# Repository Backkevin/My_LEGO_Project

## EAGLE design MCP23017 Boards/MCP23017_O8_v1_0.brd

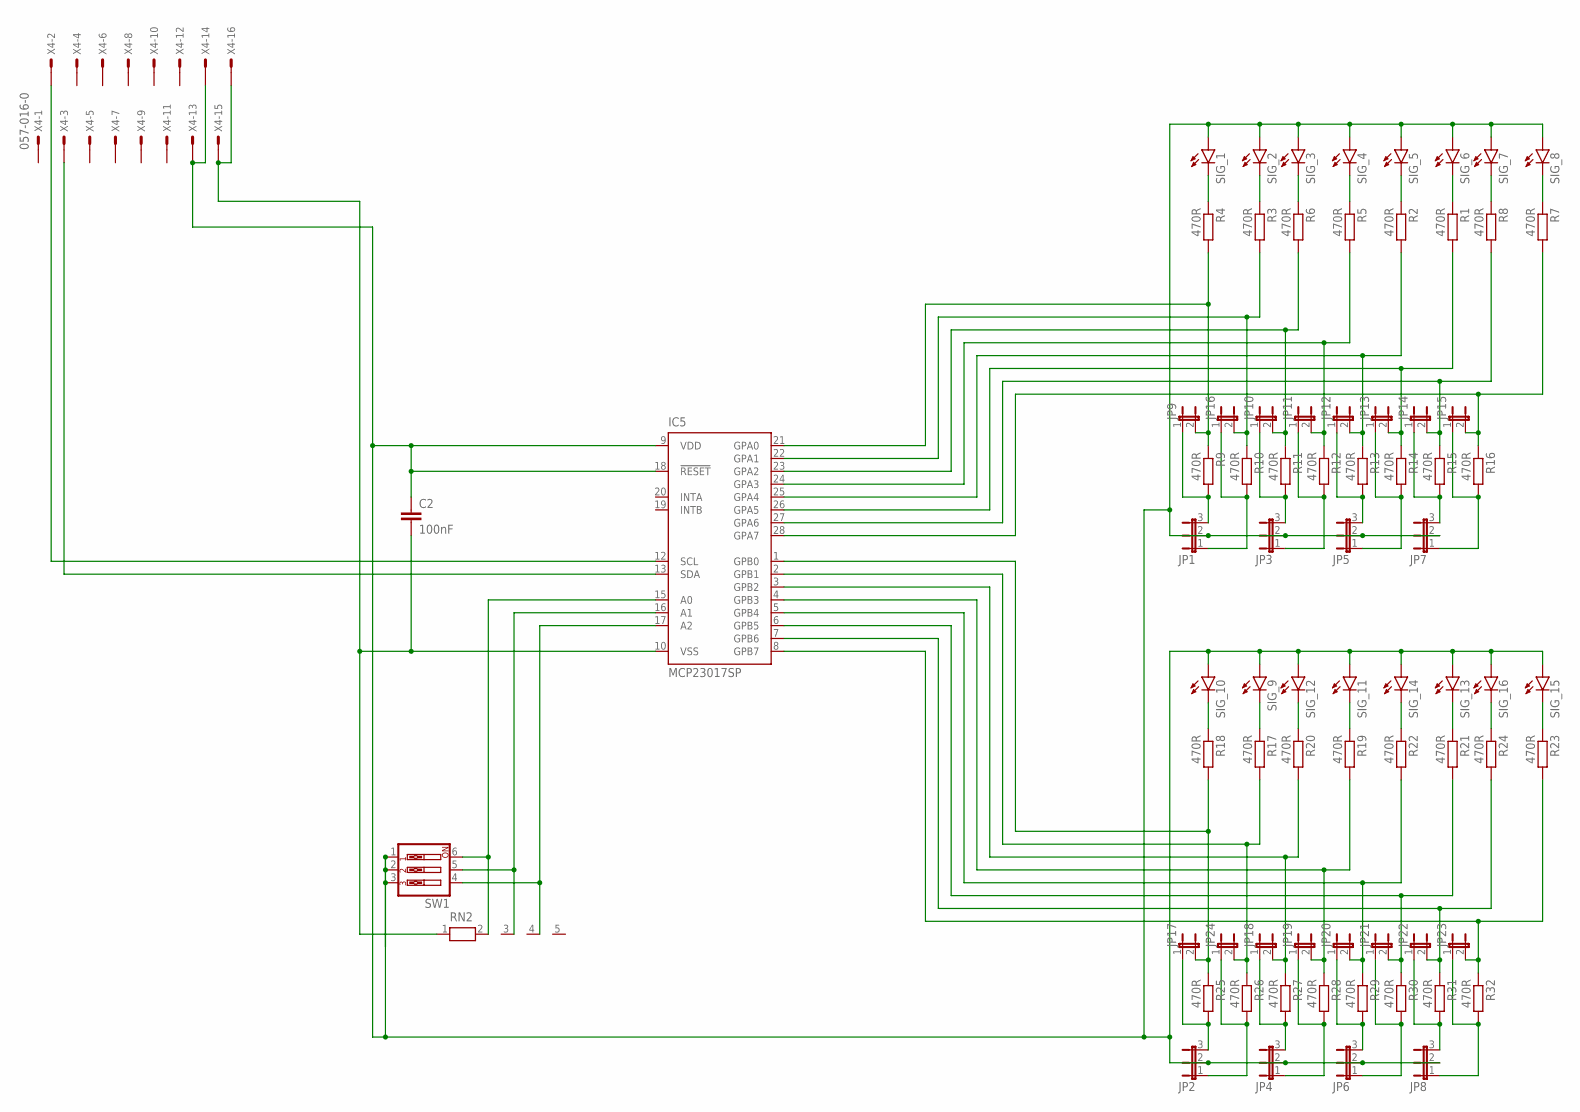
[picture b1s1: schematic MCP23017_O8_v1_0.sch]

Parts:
C2: 100nF; C025-024X044
IC5: MCP23017SP; DIL28-3
JP1, JP2, JP3, JP4, JP5, JP6, JP7, JP8: JP2E; JP2
JP9, JP10, JP11, JP12, JP13, JP14, JP15, JP16, JP17, JP18, JP19, JP20, JP21, JP22, JP23, JP24: JP1E; JP1
R1, R2, R3, R4, R5, R6, R7, R8, R9, R10, R11, R12, R13, R14, R15, R16, R17, R18, R19, R20, R21, R22, R23, R24, R25, R26, R27, R28, R29, R30, R31, R32: 470R; 0309/10
RN2: RN04; RN-5
SIG_1, SIG_2, SIG_3, SIG_4, SIG_5, SIG_6, SIG_7, SIG_8, SIG_9, SIG_10, SIG_11, SIG_12, SIG_13, SIG_14, SIG_15, SIG_16: LED3MM
SW1: SW_DIP-3; EDG-03
X4: 057-016-0

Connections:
GND2: C2.2, IC5.10 (VSS), RN2.1, X4.15, X4.16
unnamed: JP1.3, JP9.1, R9.2
unnamed: R2.1, SIG_5.K (C)
unnamed: R1.1, SIG_6.K (C)
unnamed: IC5.27 (GPA6), JP14.2, R8.2, R15.1
unnamed: IC5.17 (A2), RN2.4, SW1.4
unnamed: R8.1, SIG_7.K (C)
unnamed: R7.1, SIG_8.K (C)
unnamed: JP1.1, JP16.1, R10.2
unnamed: JP3.3, JP10.1, R11.2
unnamed: JP3.1, JP11.1, R12.2
unnamed: JP5.3, JP12.1, R13.2
unnamed: IC5.22 (GPA1), JP16.2, R3.2, R10.1
unnamed: IC5.24 (GPA3), JP11.2, R5.2, R12.1
unnamed: IC5.26 (GPA5), JP13.2, R1.2, R14.1
unnamed: IC5.28 (GPA7), JP15.2, R7.2, R16.1
unnamed: IC5.21 (GPA0), JP9.2, R4.2, R9.1
unnamed: JP5.1, JP13.1, R14.2
unnamed: JP7.3, JP14.1, R15.2
unnamed: JP7.1, JP15.1, R16.2
unnamed: IC5.16 (A1), RN2.3, SW1.5
unnamed: R4.1, SIG_1.K (C)
unnamed: R3.1, SIG_2.K (C)
unnamed: IC5.23 (GPA2), JP10.2, R6.2, R11.1
unnamed: IC5.25 (GPA4), JP12.2, R2.2, R13.1
unnamed: IC5.1 (GPB0), JP17.2, R18.2, R25.1
unnamed: IC5.3 (GPB2), JP18.2, R20.2, R27.1
unnamed: R6.1, SIG_3.K (C)
unnamed: R5.1, SIG_4.K (C)
unnamed: IC5.6 (GPB5), JP21.2, R21.2, R30.1
unnamed: IC5.8 (GPB7), JP23.2, R23.2, R32.1
unnamed: IC5.2 (GPB1), JP24.2, R17.2, R26.1
unnamed: R18.1, SIG_10.K (C)
unnamed: R17.1, SIG_9.K (C)
unnamed: IC5.4 (GPB3), JP19.2, R19.2, R28.1
unnamed: IC5.5 (GPB4), JP20.2, R22.2, R29.1
unnamed: R20.1, SIG_12.K (C)
unnamed: R19.1, SIG_11.K (C)
unnamed: R22.1, SIG_14.K (C)
unnamed: R21.1, SIG_13.K (C)
unnamed: IC5.7 (GPB6), JP22.2, R24.2, R31.1
unnamed: R24.1, SIG_16.K (C)
unnamed: R23.1, SIG_15.K (C)
unnamed: JP2.3, JP17.1, R25.2
unnamed: JP2.1, JP24.1, R26.2
unnamed: JP4.3, JP18.1, R27.2
unnamed: JP4.1, JP19.1, R28.2
unnamed: JP6.3, JP20.1, R29.2
unnamed: JP6.1, JP21.1, R30.2
unnamed: JP8.3, JP22.1, R31.2
unnamed: JP8.1, JP23.1, R32.2
unnamed: IC5.12 (SCL), X4.2
unnamed: IC5.13 (SDA), X4.3
unnamed: IC5.15 (A0), RN2.2, SW1.6
VCC5.1: C2.1, IC5.9 (VDD), IC5.18 (!RESET), JP1.2, JP2.2, JP3.2, JP4.2, JP5.2, JP6.2, JP7.2, JP8.2, SIG_1.A, SIG_2.A, SIG_3.A, SIG_4.A, SIG_5.A, SIG_6.A, SIG_7.A, SIG_8.A, SIG_9.A, SIG_10.A, SIG_11.A, SIG_12.A, SIG_13.A, SIG_14.A, SIG_15.A, SIG_16.A, SW1.1, SW1.2, SW1.3, X4.13, X4.14

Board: 2 copper layers, 77 parts (0 on the bottom side), 55 nets, no tracks yet.

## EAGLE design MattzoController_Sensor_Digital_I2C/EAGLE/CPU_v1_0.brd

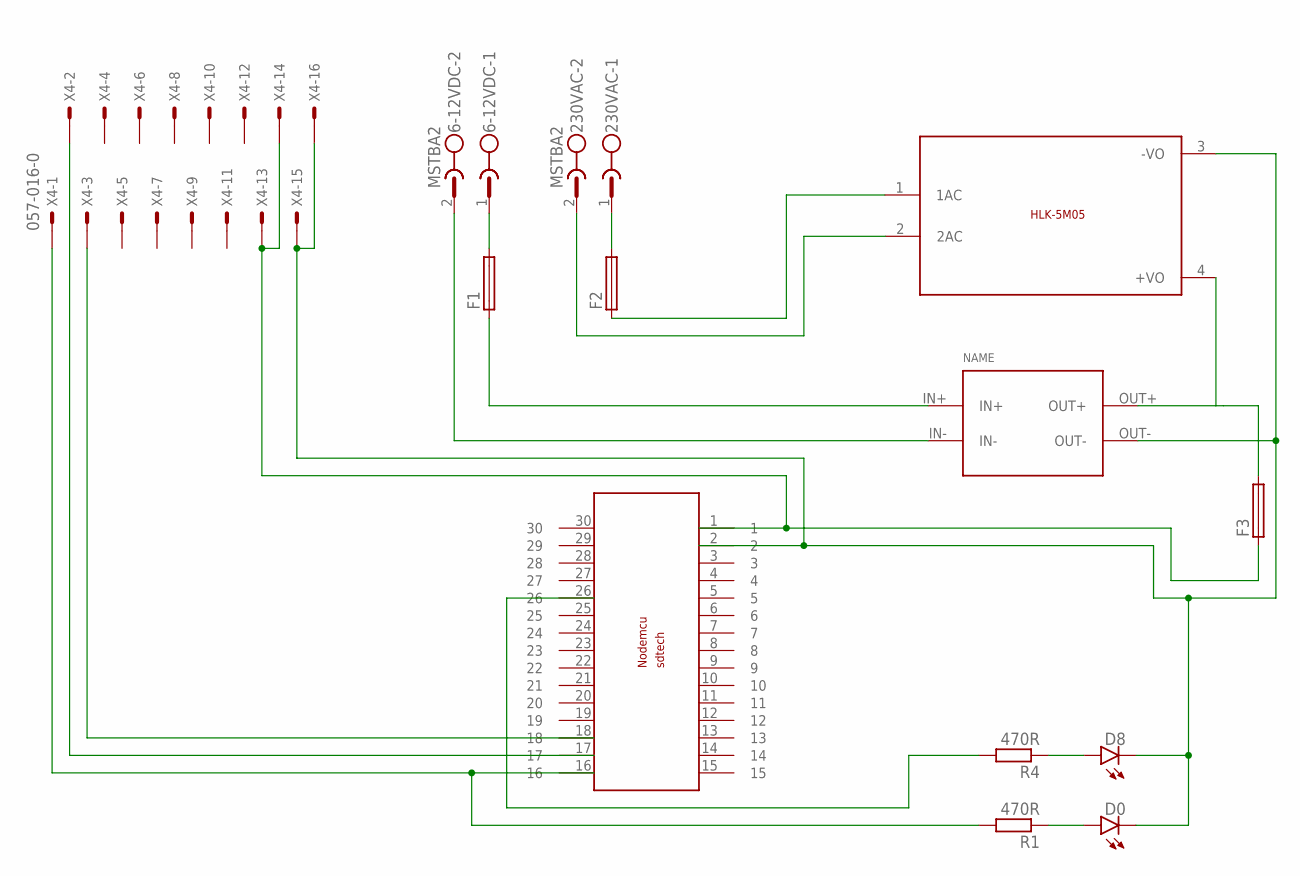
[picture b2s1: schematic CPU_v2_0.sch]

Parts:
6-12VDC, 230VAC: MSTBA2
D0, D8: LED3MM
F1, F2, F3: SH22,5A
R1, R4: 470R; 0309/10
U$1: NODEMCUESP8266
U$2: CP8-ADJ
U$3: 5VDC/5W; HLK-5M05
X4: 057-016-0

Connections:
+5VDC: F3.1, U$1.1, X4.13, X4.14
D0: R1.2, U$1.16, X4.1
D8: R4.2, U$1.26
GND: D0.K (C), D8.K (C), U$1.2, U$2.OUT-, U$3.3 (-VO), X4.15, X4.16
unnamed: D8.A, R4.1
unnamed: F3.2, U$2.OUT+, U$3.4 (+VO)
unnamed: D0.A, R1.1
unnamed: 230VAC.1, F2.2
unnamed: F2.1, U$3.1 (1AC)
unnamed: 230VAC.2, U$3.2 (2AC)
unnamed: 6-12VDC.1, F1.2
unnamed: F1.1, U$2.IN+
unnamed: 6-12VDC.2, U$2.IN-
SCL: U$1.17, X4.2
SDA: U$1.18, X4.3

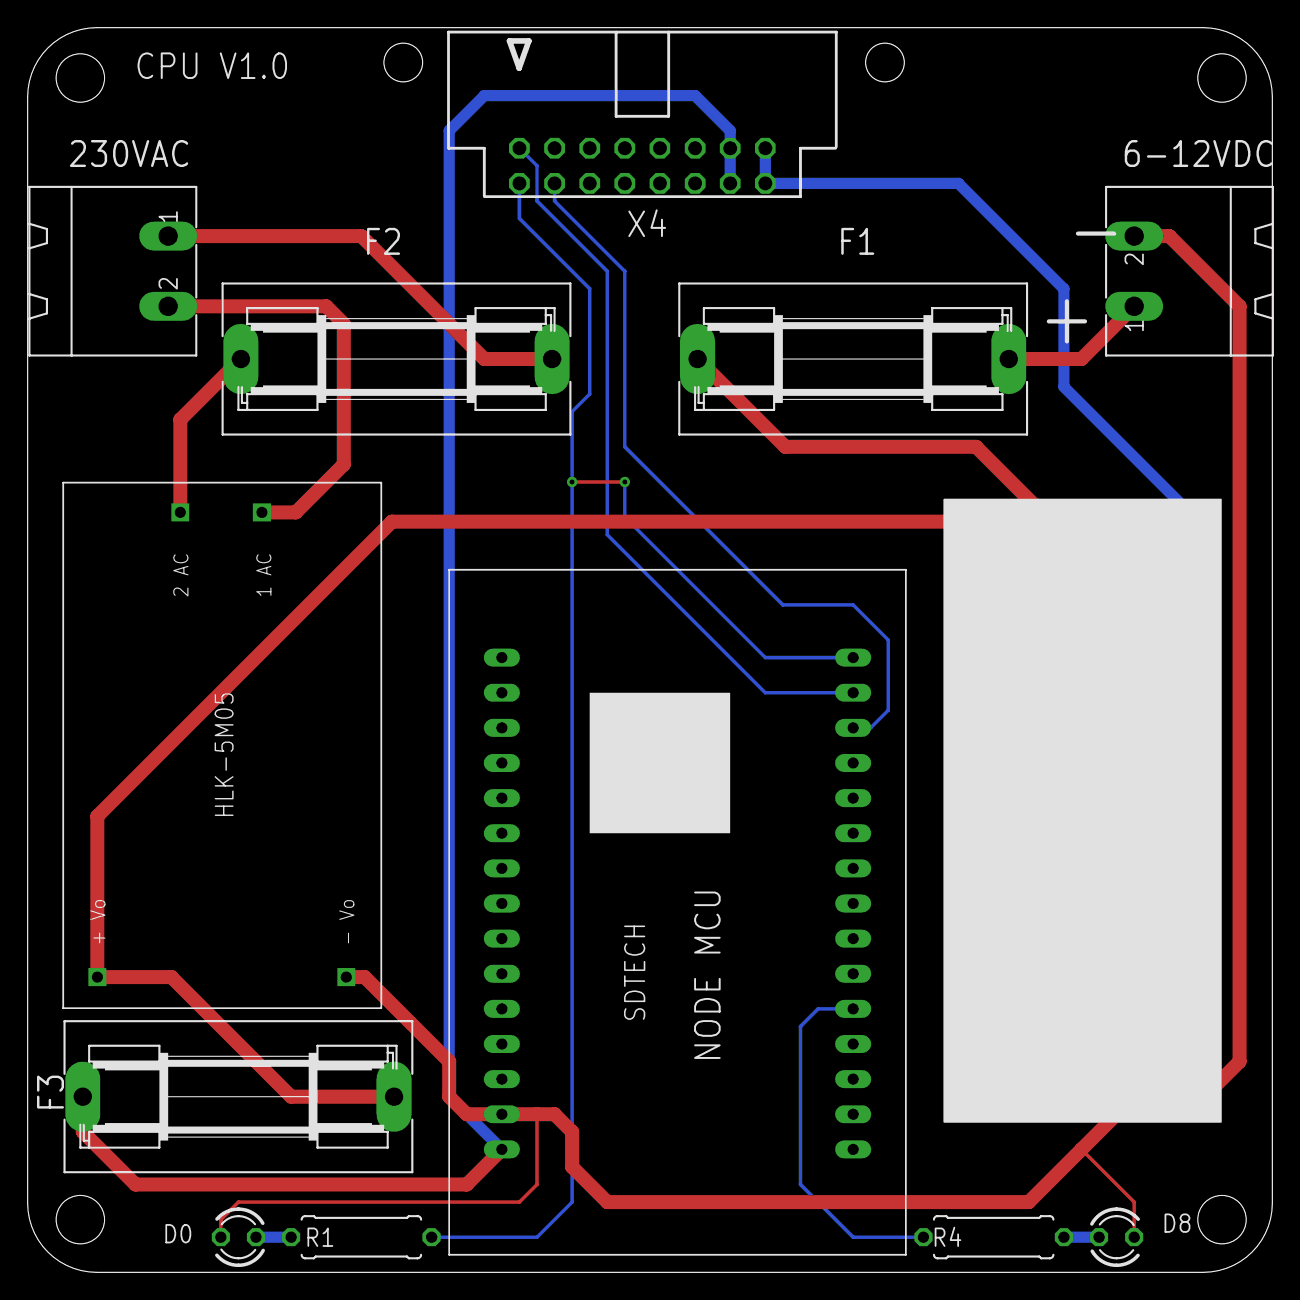
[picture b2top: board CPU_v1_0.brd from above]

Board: 2 copper layers, 90.0 x 90.0 mm, 13 parts (0 on the bottom side), 15 nets.

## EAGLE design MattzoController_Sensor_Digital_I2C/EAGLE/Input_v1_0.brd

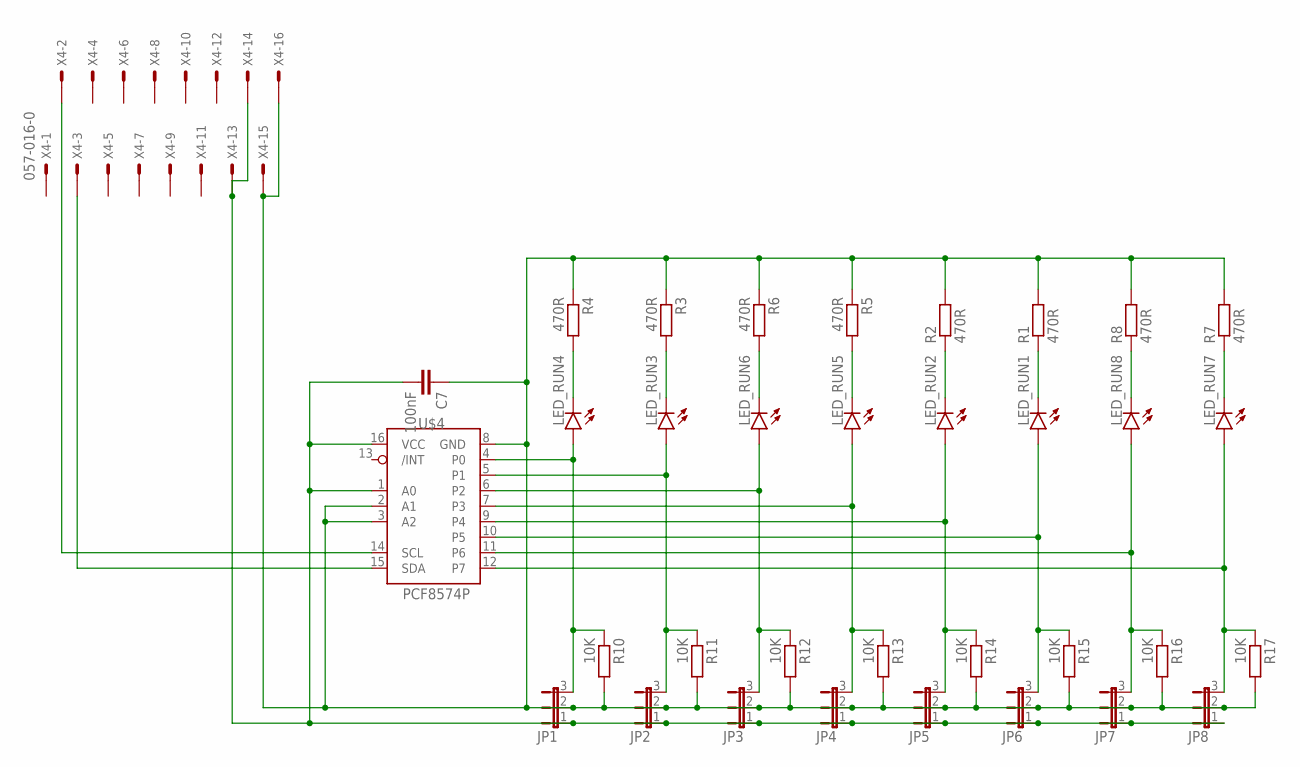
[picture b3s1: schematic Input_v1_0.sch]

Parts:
C7: 100nF; C025-024X044
JP1, JP2, JP3, JP4, JP5, JP6, JP7, JP8: JP2E; JP2
LED_RUN1, LED_RUN2, LED_RUN3, LED_RUN4, LED_RUN5, LED_RUN6, LED_RUN7, LED_RUN8: LED3MM
R1, R2, R3, R4, R5, R6, R7, R8: 470R; 0309/10
R10, R11, R12, R13, R14, R15, R16, R17: 10K; 0309/10
U$4: PCF8574P; DIL16
X4: 057-016-0

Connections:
GND1: C7.1, JP1.2, JP2.2, JP3.2, JP4.2, JP5.2, JP6.2, JP7.2, JP8.2, R1.2, R2.2, R3.1, R4.1, R5.1, R6.1, R7.2, R8.2, R10.2, R11.2, R12.2, R13.2, R14.2, R15.2, R16.2, R17.2, U$4.2 (A1), U$4.3 (A2), U$4.8 (GND), X4.15, X4.16
unnamed: LED_RUN7.K (C), R7.1
unnamed: LED_RUN8.K (C), R8.1
unnamed: LED_RUN1.K (C), R1.1
unnamed: LED_RUN2.K (C), R2.1
unnamed: LED_RUN5.K (C), R5.2
unnamed: LED_RUN6.K (C), R6.2
unnamed: LED_RUN3.K (C), R3.2
unnamed: LED_RUN4.K (C), R4.2
unnamed: U$4.15 (SDA), X4.3
unnamed: JP1.3, LED_RUN4.A, R10.1, U$4.4 (P0)
unnamed: JP2.3, LED_RUN3.A, R11.1, U$4.5 (P1)
unnamed: JP3.3, LED_RUN6.A, R12.1, U$4.6 (P2)
unnamed: JP4.3, LED_RUN5.A, R13.1, U$4.7 (P3)
unnamed: JP5.3, LED_RUN2.A, R14.1, U$4.9 (P4)
unnamed: JP6.3, LED_RUN1.A, R15.1, U$4.10 (P5)
unnamed: JP7.3, LED_RUN8.A, R16.1, U$4.11 (P6)
unnamed: JP8.3, LED_RUN7.A, R17.1, U$4.12 (P7)
SCL: U$4.14 (SCL), X4.2
VCC5.0: C7.2, JP1.1, JP2.1, JP3.1, JP4.1, JP5.1, JP6.1, JP7.1, JP8.1, U$4.1 (A0), U$4.16 (VCC), X4.13, X4.14

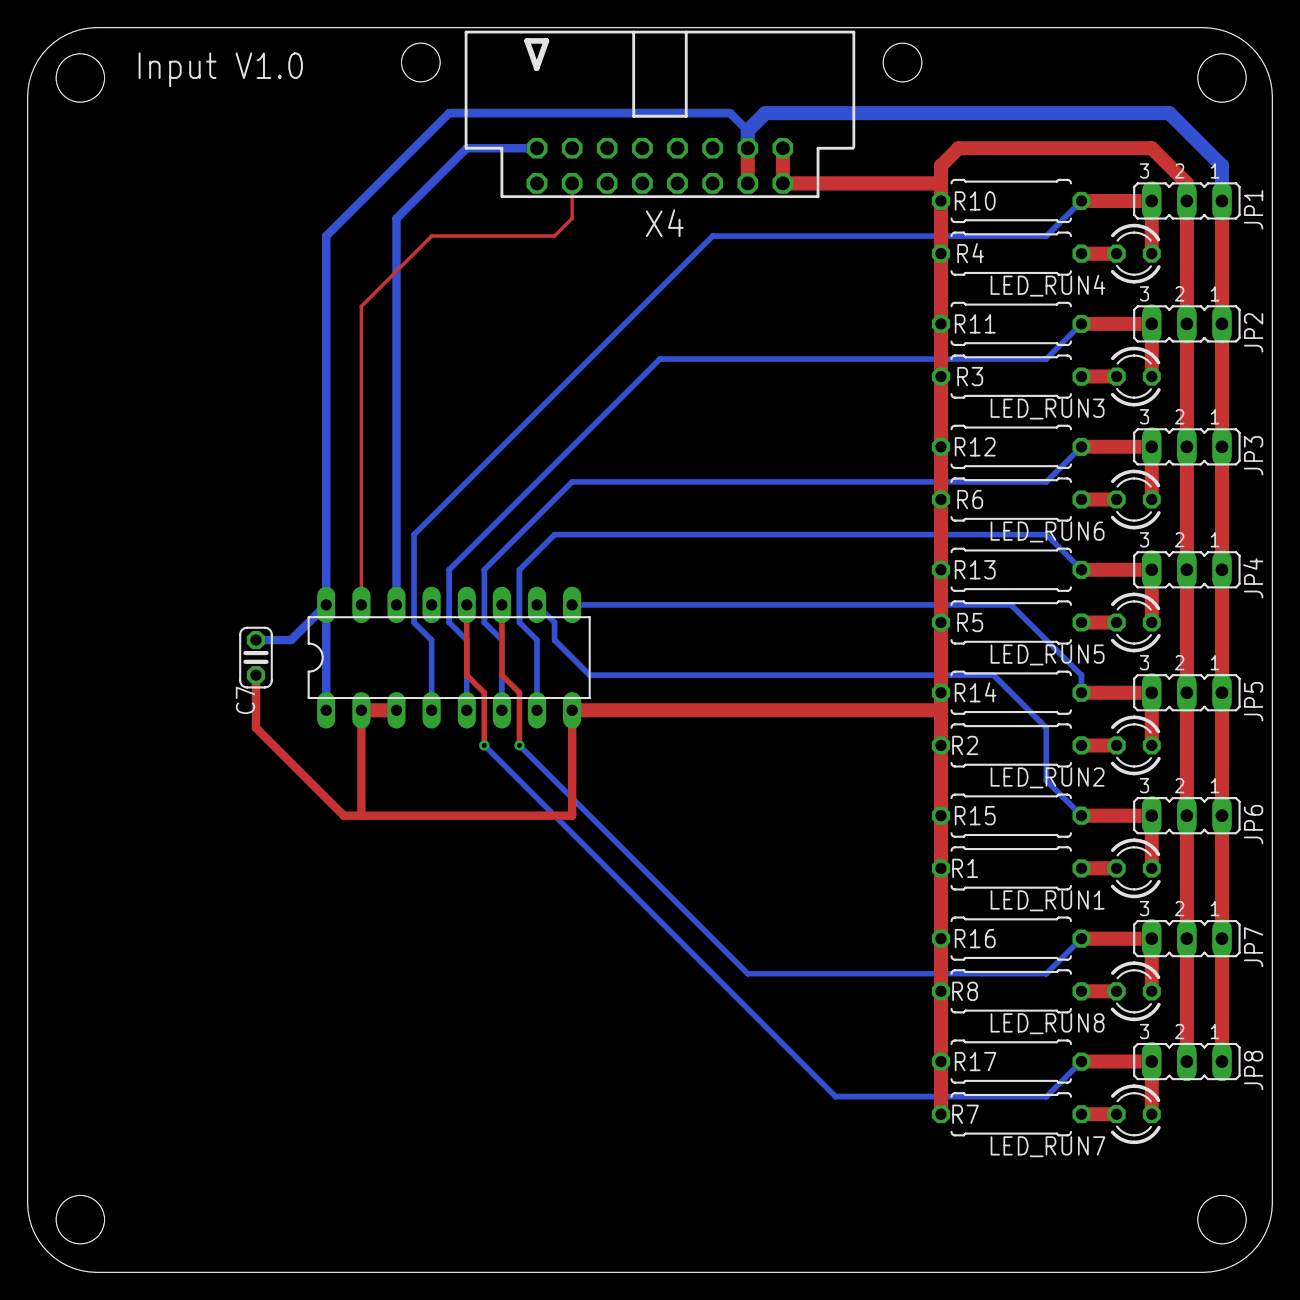
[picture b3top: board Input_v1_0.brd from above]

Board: 2 copper layers, 90.0 x 90.0 mm, 35 parts (0 on the bottom side), 20 nets.

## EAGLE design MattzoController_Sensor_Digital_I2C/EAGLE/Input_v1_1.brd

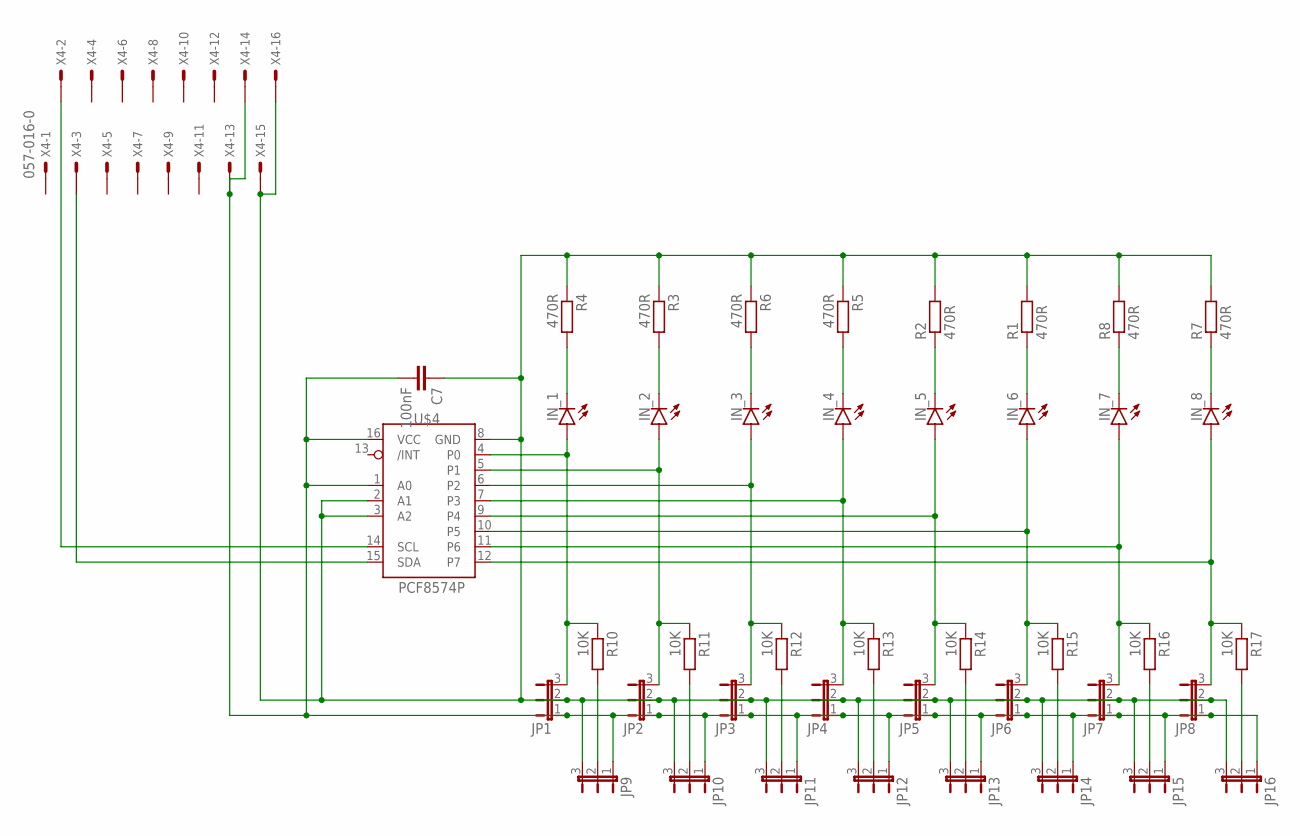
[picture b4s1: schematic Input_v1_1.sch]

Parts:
C7: 100nF; C025-024X044
IN_1, IN_2, IN_3, IN_4, IN_5, IN_6, IN_7, IN_8: LED3MM
JP1, JP2, JP3, JP4, JP5, JP6, JP7, JP8, JP9, JP10, JP11, JP12, JP13, JP14, JP15, JP16: JP2E; JP2
R1, R2, R3, R4, R5, R6, R7, R8: 470R; 0309/10
R10, R11, R12, R13, R14, R15, R16, R17: 10K; 0309/10
U$4: PCF8574P; DIL16
X4: 057-016-0

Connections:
GND1: C7.1, JP1.2, JP2.2, JP3.2, JP4.2, JP5.2, JP6.2, JP7.2, JP8.2, JP9.3, JP10.3, JP11.3, JP12.3, JP13.3, JP14.3, JP15.3, JP16.3, R1.2, R2.2, R3.1, R4.1, R5.1, R6.1, R7.2, R8.2, U$4.2 (A1), U$4.3 (A2), U$4.8 (GND), X4.15, X4.16
unnamed: IN_8.K (C), R7.1
unnamed: IN_7.K (C), R8.1
unnamed: IN_6.K (C), R1.1
unnamed: IN_5.K (C), R2.1
unnamed: IN_4.K (C), R5.2
unnamed: IN_3.K (C), R6.2
unnamed: IN_2.K (C), R3.2
unnamed: IN_1.K (C), R4.2
unnamed: U$4.15 (SDA), X4.3
unnamed: JP9.2, R10.2
unnamed: JP10.2, R11.2
unnamed: JP11.2, R12.2
unnamed: JP12.2, R13.2
unnamed: JP13.2, R14.2
unnamed: JP14.2, R15.2
unnamed: JP15.2, R16.2
unnamed: JP16.2, R17.2
unnamed: IN_1.A, JP1.3, R10.1, U$4.4 (P0)
unnamed: IN_2.A, JP2.3, R11.1, U$4.5 (P1)
unnamed: IN_3.A, JP3.3, R12.1, U$4.6 (P2)
unnamed: IN_4.A, JP4.3, R13.1, U$4.7 (P3)
unnamed: IN_5.A, JP5.3, R14.1, U$4.9 (P4)
unnamed: IN_6.A, JP6.3, R15.1, U$4.10 (P5)
unnamed: IN_7.A, JP7.3, R16.1, U$4.11 (P6)
unnamed: IN_8.A, JP8.3, R17.1, U$4.12 (P7)
SCL: U$4.14 (SCL), X4.2
VCC5.0: C7.2, JP1.1, JP2.1, JP3.1, JP4.1, JP5.1, JP6.1, JP7.1, JP8.1, JP9.1, JP10.1, JP11.1, JP12.1, JP13.1, JP14.1, JP15.1, JP16.1, U$4.1 (A0), U$4.16 (VCC), X4.13, X4.14

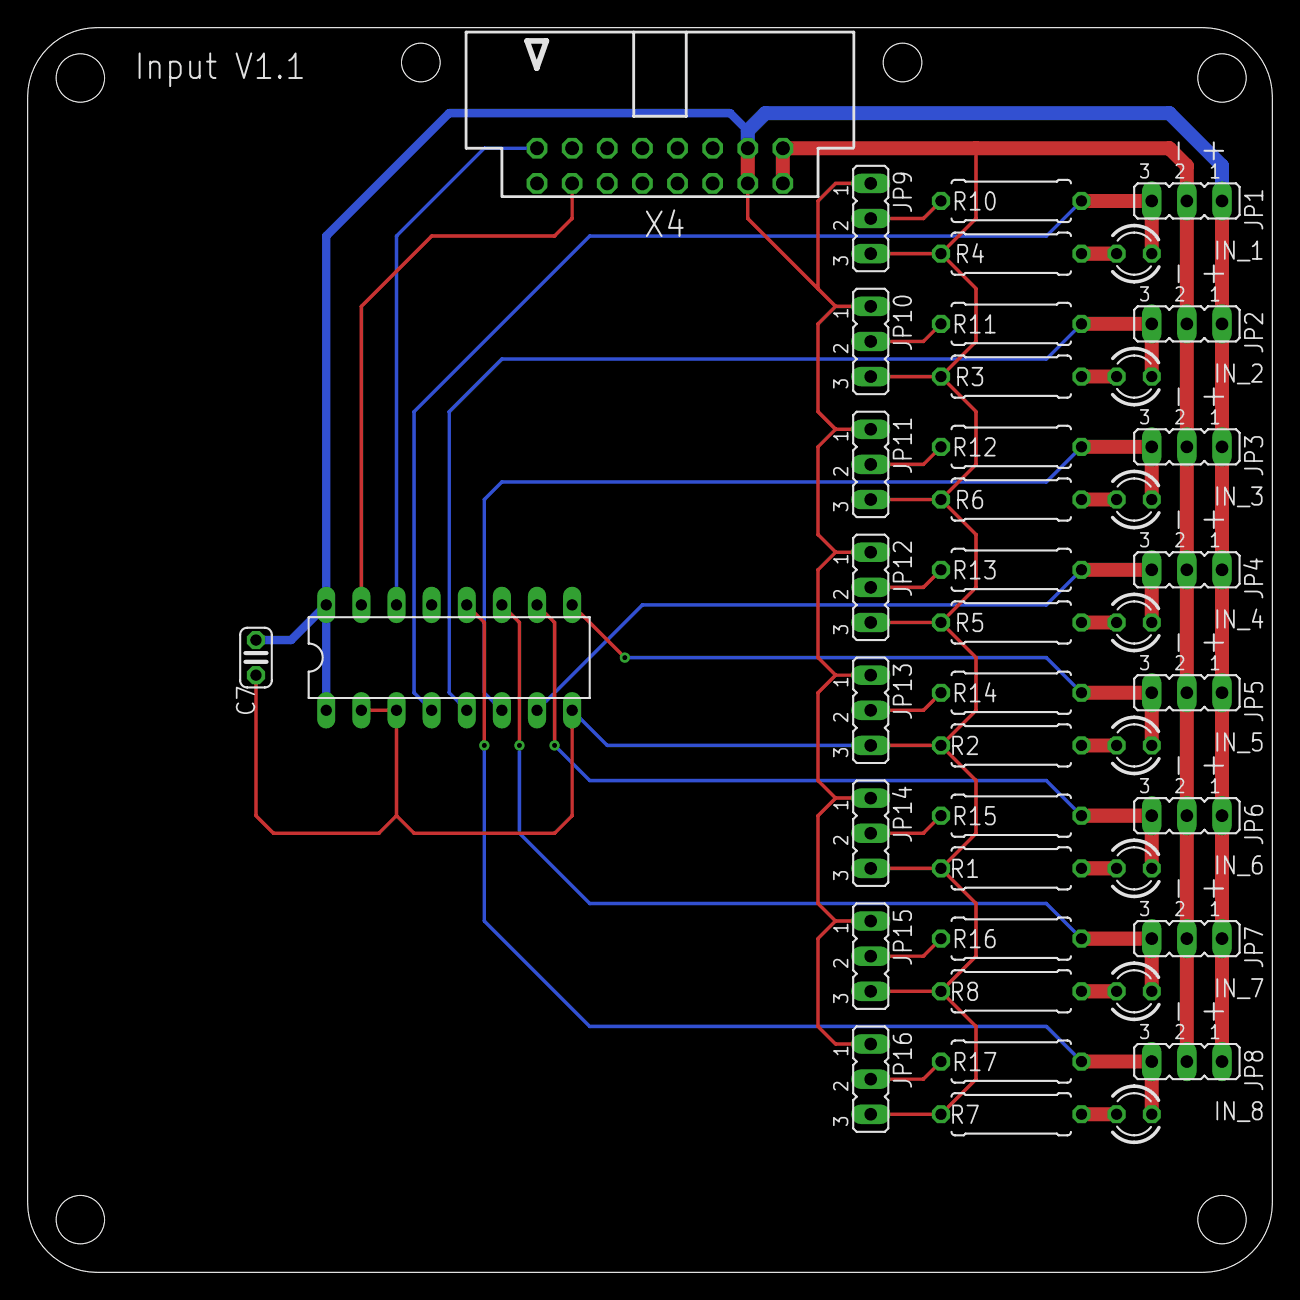
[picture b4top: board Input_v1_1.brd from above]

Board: 2 copper layers, 90.0 x 90.0 mm, 43 parts (0 on the bottom side), 28 nets.
